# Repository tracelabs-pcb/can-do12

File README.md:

# CAN-DO12 — 24V Aktor-Modul (12x High-Side Digital Outputs)

**Status: PCB-Design abgeschlossen — unbestückt**  
**Tool:** KiCad | **Layer:** 4-Layer | **Hersteller-ready:** Ja

---

## Projektbeschreibung

Kompaktes 24V-Aktormodul zur Ansteuerung von 12 digitalen Lasten 
im Labor- und Prüfstandsbetrieb. Ansteuerung über CAN 2.0B, 
zusätzlich USB-C Service-Port für Parametrierung und Diagnose.
Entwickelt als Prototyp für Prüfstands- und Sondermaschinenbau.

**Besonderheiten:**
- 12x High-Side Ausgänge (24V / 1A je Kanal)
- CAN 2.0B (1 Mbit/s) + USB-C Full-Speed Device
- TVS + Verpolschutz am 24V Eingang
- ESD-Schutz an CAN und USB
- 4-Layer Layout, 140×80mm, Hutschienen-tauglich

---

## Hardware

| Komponente | Beschreibung |
|---|---|
| MCU | USB FS + CAN (STM32-Familie) |
| Ausgangstreiber | 12x High-Side, 24V |
| Schnittstellen | CAN 2.0B, USB-C, SWD |
| Versorgung | 18…30V DC, Buck → 3.3V |
| Schutz | TVS, Verpolschutz, ESD |
| Stackup | 4-Layer (Signal / GND / PWR / Signal) |
| Tool | KiCad |

---

## Anschlüsse

- USB-C (kurze Kante, mittig)
- DE-9 CAN-Stecker
- 2-pol Schraubklemme 24V Eingang
- 2x 8-pol Schraubklemme Ausgänge
- SWD Header (2.54mm)
- Jumper CAN-Terminierung 120Ω

---

## Ausschlüsse

Kein Serienprodukt — kein CE/EMV, keine Safety-Anwendung,
keine galvanische Trennung, keine Firmware.

---

## Dateien in diesem Repository

- `/kicad/` — KiCad Projektdateien
- `/screenshots/` — PCB- und Schematic-Ansichten

---

> Entwickelt von [Shawn Schneider](https://tracelabs-pcb.de)  
> — PCB-Design & Lötservice, Wolfsburg

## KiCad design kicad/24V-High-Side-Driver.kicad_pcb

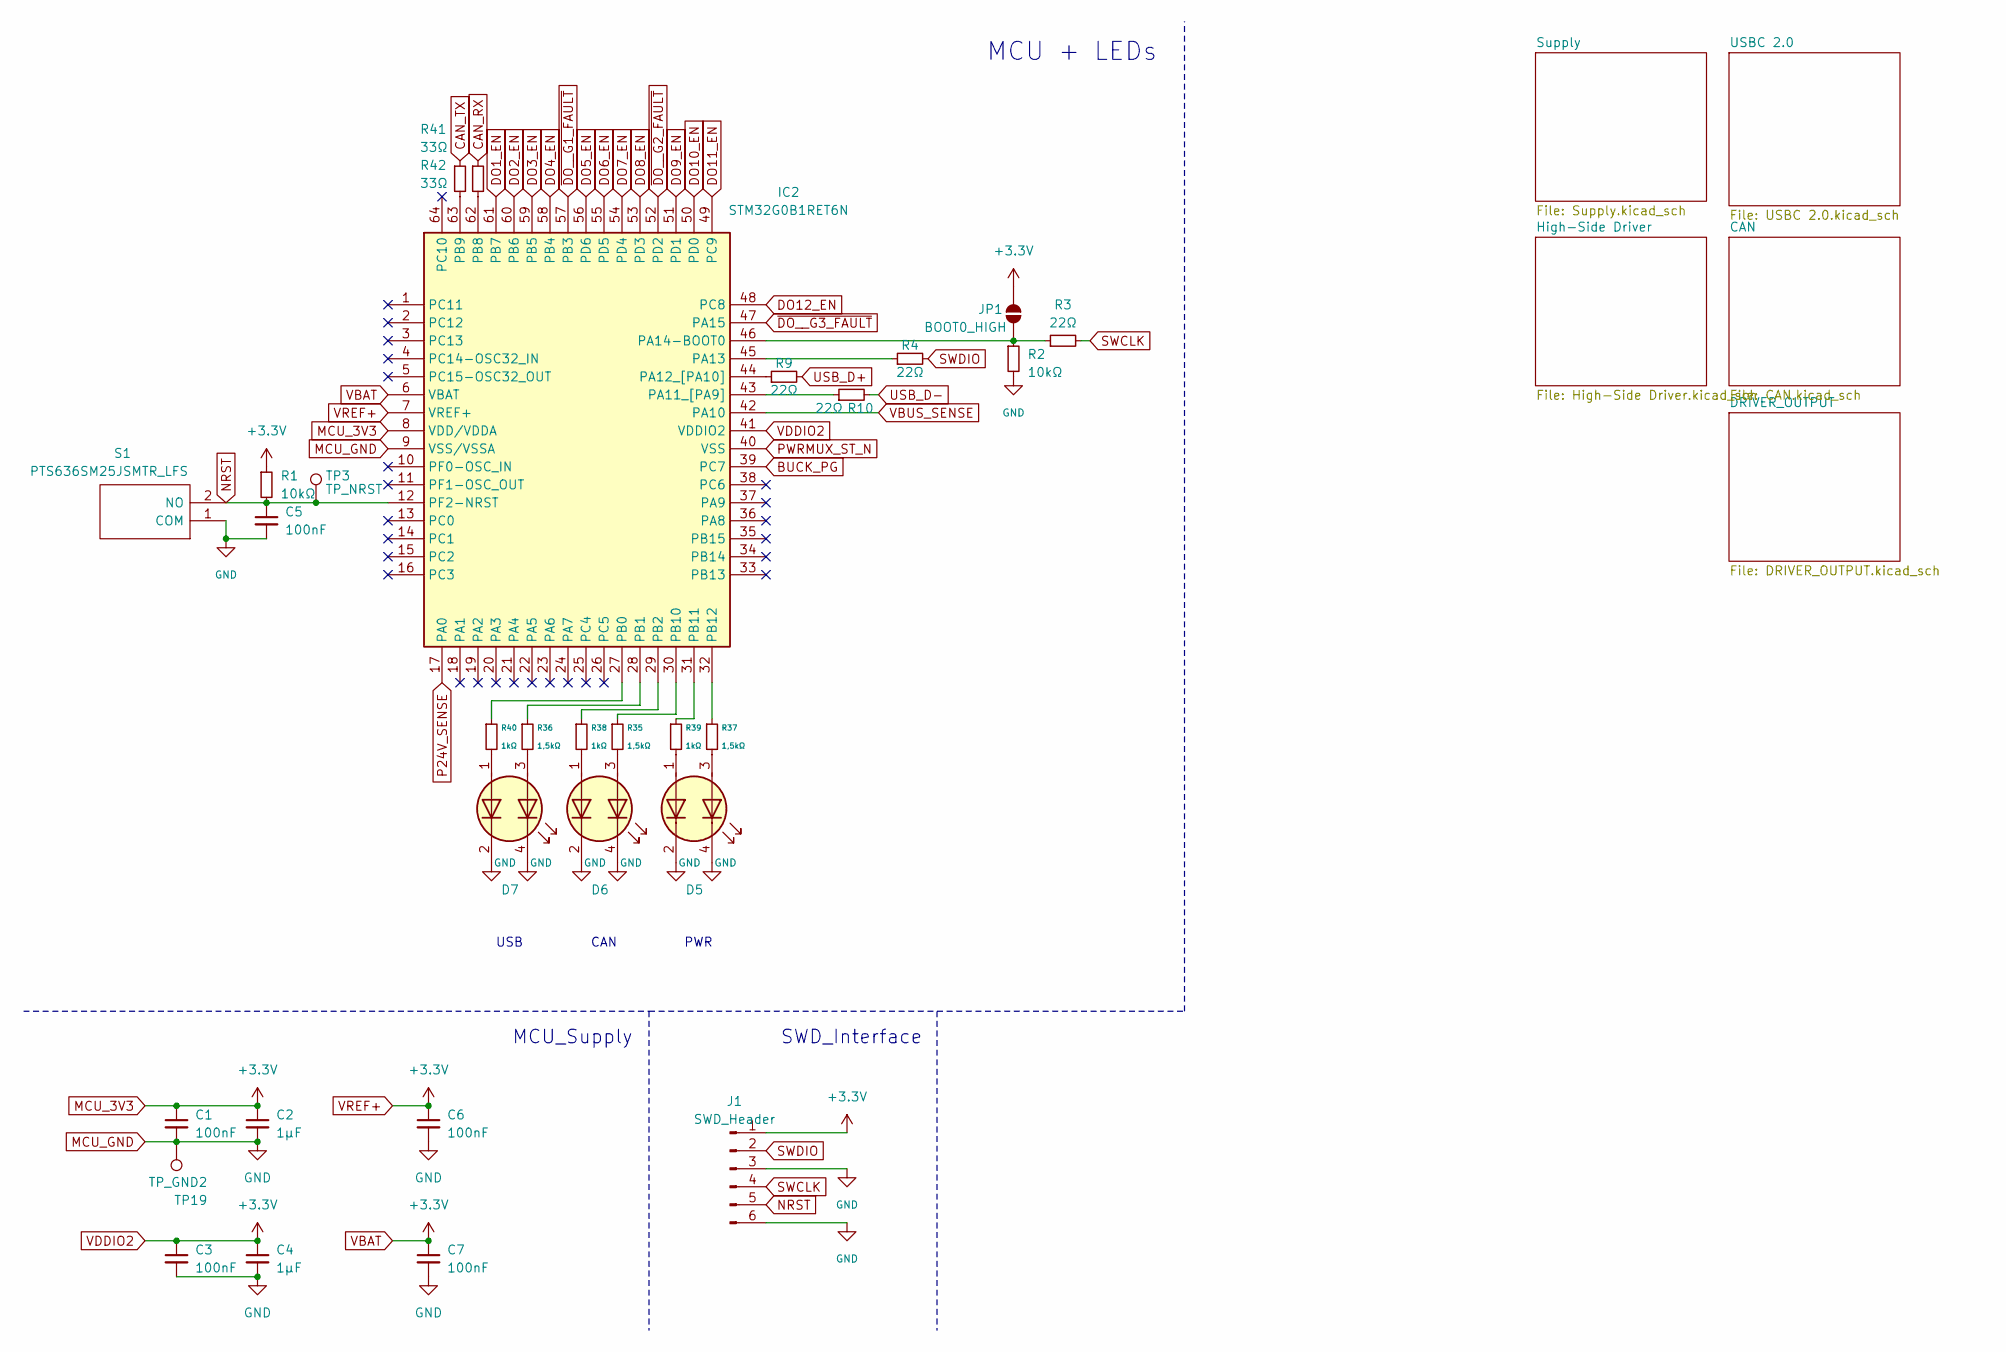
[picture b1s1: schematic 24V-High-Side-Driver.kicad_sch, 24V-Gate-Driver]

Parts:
C1, C3, C5, C6, C7: 100nF; C_0603_1608Metric
C2, C4: 1µF; C_0603_1608Metric
D5, D6, D7: APTBD3216SURKCGKC-01; APTBD3216SURKCGKC01
IC2: STM32G0B1RET6N; QFP50P1200X1200X160-64N; Mouser Part Number 511-STM32G0B1RET6N
J1: SWD_Header; PinHeader_1x06_P2.54mm_Vertical
JP1: BOOT0_HIGH; SolderJumper-2_P1.3mm_Open_RoundedPad1.0x1.5mm
R1, R2: 10kΩ; R_0603_1608Metric
R3, R4, R9, R10: 22Ω; R_0603_1608Metric
R35, R36, R37: 1,5kΩ; R_0603_1608Metric
R38, R39, R40: 1kΩ; R_0603_1608Metric
R41, R42: 33Ω; R_0603_1608Metric
S1: PTS636SM25JSMTR_LFS; PTS636SM25JSMTRLFS; Manufacturer_Part_Number PTS636SM25JSMTR LFS
TP3: TP_NRST; TestPoint_Pad_D1.5mm
TP19: TP_GND2; TestPoint_Pad_D1.5mm

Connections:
BUCK_PG: IC2.39 (PC7); also elsewhere on the board
CAN_RX: R41.1; also elsewhere on the board
CAN_TX: R42.1; also elsewhere on the board
DO1_EN: IC2.61 (PB7); also elsewhere on the board
DO2_EN: IC2.60 (PB6); also elsewhere on the board
DO3_EN: IC2.59 (PB5); also elsewhere on the board
DO4_EN: IC2.58 (PB4); also elsewhere on the board
DO5_EN: IC2.56 (PD6); also elsewhere on the board
DO6_EN: IC2.55 (PD5); also elsewhere on the board
DO7_EN: IC2.54 (PD4); also elsewhere on the board
DO8_EN: IC2.53 (PD3); also elsewhere on the board
DO9_EN: IC2.51 (PD1); also elsewhere on the board
DO10_EN: IC2.50 (PD0); also elsewhere on the board
DO11_EN: IC2.49 (PC9); also elsewhere on the board
DO12_EN: IC2.48 (PC8); also elsewhere on the board
MCU_3V3: C1.1, C2.1, C3.1, C4.1, C6.1, C7.1, IC2.6 (VBAT), IC2.7 (VREF+), IC2.8 (VDD/VDDA), IC2.41 (VDDIO2), J1.1, JP1.2 (B), R1.1; also elsewhere on the board
MCU_GND: C1.2, C2.2, C3.2, C4.2, C5.2, C6.2, C7.2, D5.2 (K1), D5.4 (K2), D6.2 (K1), D6.4 (K2), D7.2 (K1), D7.4 (K2), IC2.9 (VSS/VSSA), J1.3, J1.6, R2.2, S1.1 (COM), TP19.1; also elsewhere on the board
NRST: C5.1, IC2.12 (PF2-NRST), J1.5, R1.2, S1.2 (NO), TP3.1
unnamed: D5.1 (A1), R39.2
unnamed: D5.3 (A2), R37.2
unnamed: D6.1 (A1), R38.2
unnamed: D6.3 (A2), R35.2
unnamed: D7.1 (A1), R40.2
unnamed: D7.3 (A2), R36.2
unnamed: IC2.43 (PA11_[PA9]), R10.1
unnamed: IC2.44 (PA12_[PA10]), R9.1
unnamed: IC2.45 (PA13), R4.1
unnamed: IC2.46 (PA14-BOOT0), JP1.1 (A), R2.1, R3.1
unnamed: IC2.27 (PB0), R40.1
unnamed: IC2.28 (PB1), R36.1
unnamed: IC2.29 (PB2), R38.1
unnamed: IC2.62 (PB8), R41.2
unnamed: IC2.63 (PB9), R42.2
unnamed: IC2.30 (PB10), R35.1
unnamed: IC2.31 (PB11), R39.1
unnamed: IC2.32 (PB12), R37.1
P24V_SENSE: IC2.17 (PA0); also elsewhere on the board
PWRMUX_ST_N: IC2.40 (VSS); also elsewhere on the board
SWCLK: J1.4, R3.2
SWDIO: J1.2, R4.2
USB_D+: R9.2; also elsewhere on the board
USB_D-: R10.2; also elsewhere on the board
VBUS_SENSE: IC2.42 (PA10); also elsewhere on the board
~DO__G1_FAULT: IC2.57 (PB3); also elsewhere on the board
~DO__G2_FAULT: IC2.52 (PD2); also elsewhere on the board
~DO__G3_FAULT: IC2.47 (PA15); also elsewhere on the board

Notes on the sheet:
SWD_Interface
MCU_Supply
PWR
CAN
USB
MCU + LEDs

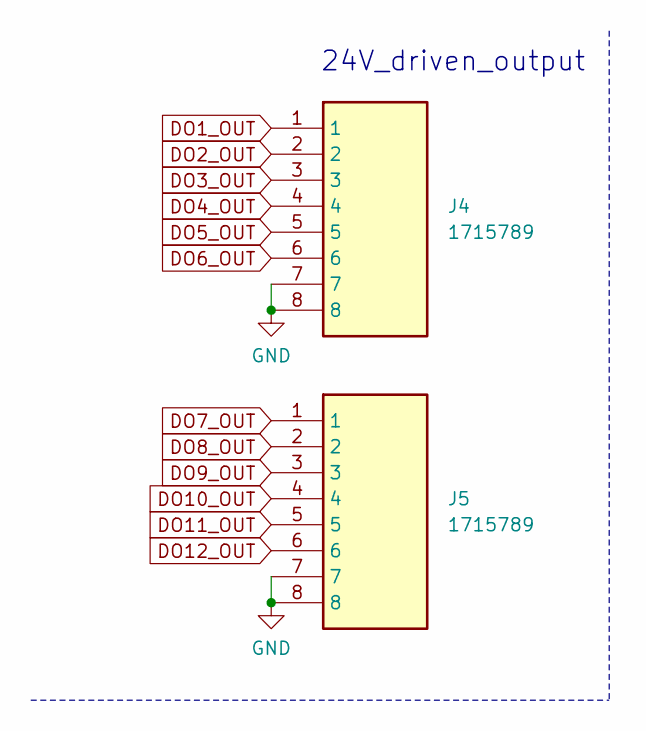
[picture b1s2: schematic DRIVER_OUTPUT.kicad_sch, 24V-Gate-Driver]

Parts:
J4, J5: 1715789; Mouser Part Number 651-1715789

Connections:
DO1_OUT: J4.1; also elsewhere on the board
DO2_OUT: J4.2; also elsewhere on the board
DO3_OUT: J4.3; also elsewhere on the board
DO4_OUT: J4.4; also elsewhere on the board
DO5_OUT: J4.5; also elsewhere on the board
DO6_OUT: J4.6; also elsewhere on the board
DO7_OUT: J5.1; also elsewhere on the board
DO8_OUT: J5.2; also elsewhere on the board
DO9_OUT: J5.3; also elsewhere on the board
DO10_OUT: J5.4; also elsewhere on the board
DO11_OUT: J5.5; also elsewhere on the board
DO12_OUT: J5.6; also elsewhere on the board
MCU_GND: J4.7, J4.8, J5.7, J5.8; also elsewhere on the board

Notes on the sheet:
24V_driven_output

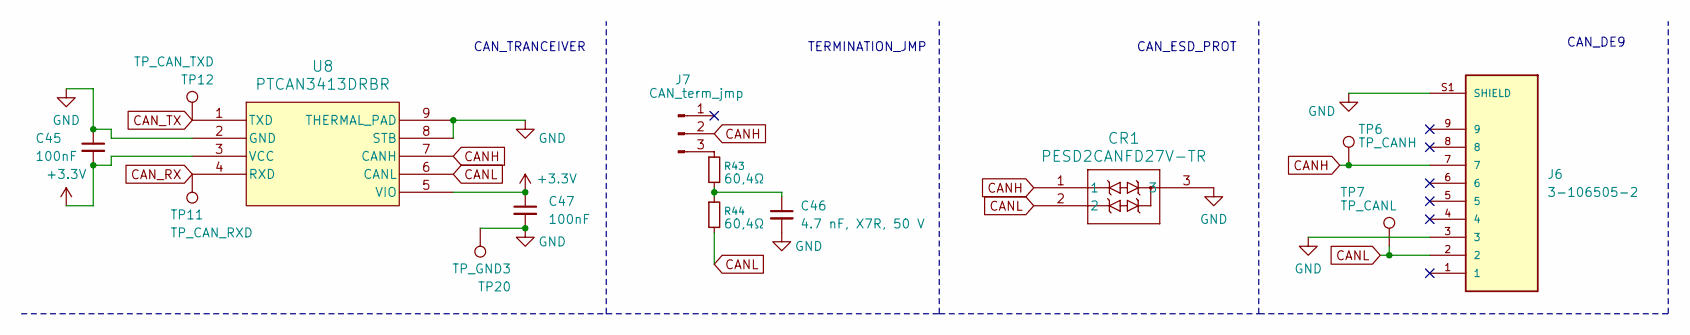
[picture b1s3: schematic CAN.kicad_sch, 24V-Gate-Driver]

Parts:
C45, C47: 100nF; C_0603_1608Metric
C46: 4.7 nF, X7R, 50 V; C_0603_1608Metric
CR1: PESD2CANFD27V-TR; SOT23_PESD2_NEX
J6: 3-106505-2; TE_3-106505-2; PART_REV M; DigiKey_Part_Number A105026-ND
J7: CAN_term_jmp; PinHeader_1x03_P2.54mm_Vertical
R43, R44: 60,4Ω; R_0603_1608Metric
TP6: TP_CANH; TestPoint_Pad_D1.5mm
TP7: TP_CANL; TestPoint_Pad_D1.5mm
TP11: TP_CAN_RXD; TestPoint_Pad_D1.5mm
TP12: TP_CAN_TXD; TestPoint_Pad_D1.5mm
TP20: TP_GND3; TestPoint_Pad_D1.5mm
U8: PTCAN3413DRBR; VSON8-DRB_TEX

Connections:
CANH: CR1.1, J6.7, J7.2, TP6.1, U8.7 (CANH)
CANL: CR1.2, J6.2, R44.2, TP7.1, U8.6 (CANL)
CAN_RX: TP11.1, U8.4 (RXD); also elsewhere on the board
CAN_TX: TP12.1, U8.1 (TXD); also elsewhere on the board
MCU_3V3: C45.2, C47.1, U8.3 (VCC), U8.5 (VIO); also elsewhere on the board
MCU_GND: C45.1, C46.2, C47.2, CR1.3, J6.3, J6.S1 (SHIELD), J6.S2 (SHIELD), TP20.1, U8.2 (GND), U8.8 (STB), U8.9 (THERMAL_PAD); also elsewhere on the board
unnamed: C46.1, R43.2, R44.1
unnamed: J7.3, R43.1

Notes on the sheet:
TERMINATION_JMP
CAN_ESD_PROT
CAN_DE9
CAN_TRANCEIVER

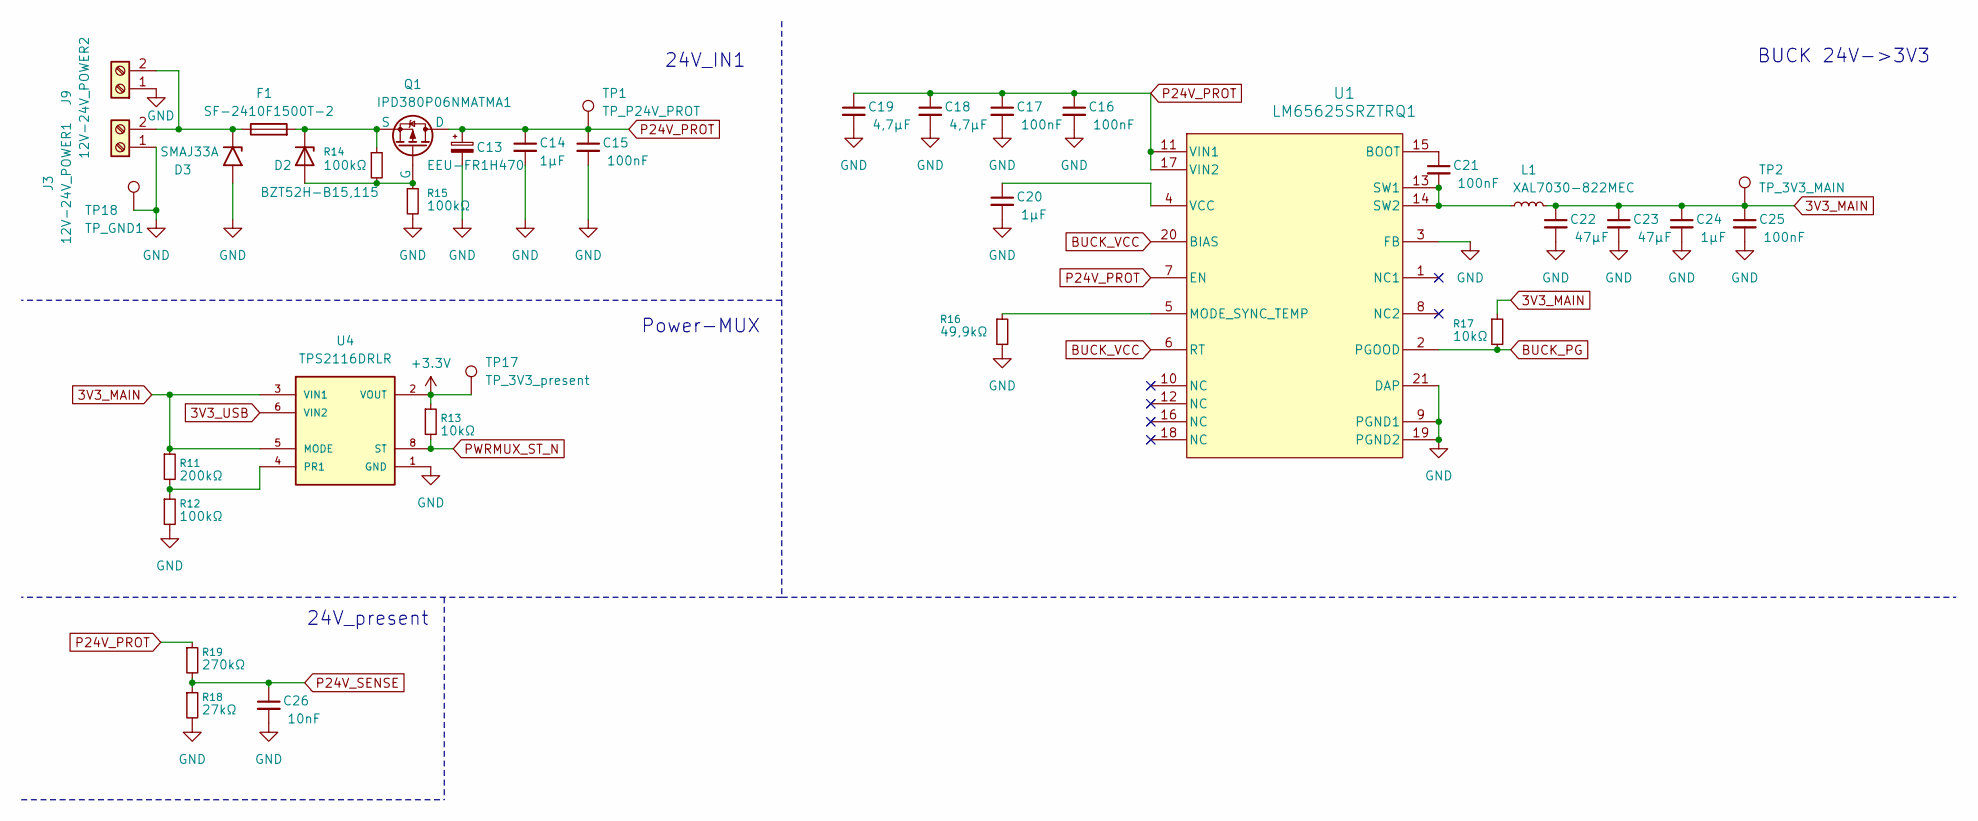
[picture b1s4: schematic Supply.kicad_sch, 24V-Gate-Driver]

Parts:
C13: EEU-FR1H470; CAPPRD250W55D630H1270
C14: 1µF; C_0805_2012Metric
C15, C16, C17, C21, C25: 100nF; C_0603_1608Metric
C18, C19: 4,7µF; C_0805_2012Metric
C20, C24: 1µF; C_0603_1608Metric
C22, C23: 47µF; C_1206_3216Metric
C26: 10nF; C_0603_1608Metric
D2: BZT52H-B15,115; D_SOD-123F
D3: SMAJ33A; D_SMA
F1: SF-2410F1500T-2; SF2410F1500T2
J3: 12V-24V_POWER1; 1729128
J9: 12V-24V_POWER2; 1729128
L1: XAL7030-822MEC; XAL7030822MEC
Q1: IPD380P06NMATMA1; PG-TO252-3-313_INF
R11: 200kΩ; R_0603_1608Metric
R12, R14, R15: 100kΩ; R_0603_1608Metric
R13, R17: 10kΩ; R_0603_1608Metric
R16: 49,9kΩ; R_0603_1608Metric
R18: 27kΩ; R_0603_1608Metric
R19: 270kΩ; R_0603_1608Metric
TP1: TP_P24V_PROT; TestPoint_Pad_D1.5mm
TP2: TP_3V3_MAIN; TestPoint_Pad_D1.5mm
TP17: TP_3V3_present; TestPoint_Pad_D1.5mm
TP18: TP_GND1; TestPoint_Pad_D1.5mm
U1: LM65625SRZTRQ1; RZT0020A-MFG
U4: TPS2116DRLR; SOTFL50P160X60-8N; PARTREV A; DigiKey_Part_Number 296-TPS2116DRLRCT-ND

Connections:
3V3_MAIN: C22.1, C23.1, C24.1, C25.1, L1.2, R11.1, R17.1, TP2.1, U4.3 (VIN1), U4.5 (MODE)
3V3_USB: U4.6 (VIN2); also elsewhere on the board
BUCK_PG: R17.2, U1.2 (PGOOD); also elsewhere on the board
BUCK_VCC: U1.6 (RT), U1.20 (BIAS)
MCU_3V3: R13.1, TP17.1, U4.2 (VOUT), U4.7 (VOUT); also elsewhere on the board
MCU_GND: C13.2, C14.2, C15.2, C16.2, C17.2, C18.2, C19.2, C20.2, C22.2, C23.2, C24.2, C25.2, C26.2, D3.2 (A2), J3.1, J9.1, R12.2, R15.2, R16.2, R18.2, TP18.1, U1.3 (FB), U1.9 (PGND1), U1.19 (PGND2), U1.21 (DAP), U1.22 (DAP), U1.23 (DAP), U1.24 (DAP), U1.25 (DAP), U1.26 (DAP), U1.27 (DAP), U4.1 (GND); also elsewhere on the board
unnamed: D2.2 (A), Q1.1 (G), R14.2, R15.1
unnamed: D2.1 (K), F1.2, Q1.3 (S), R14.1
unnamed: D3.1 (A1), F1.1, J3.2, J9.2
unnamed: C21.1, U1.15 (BOOT)
unnamed: R16.1, U1.5 (MODE_SYNC_TEMP)
unnamed: C21.2, L1.1, U1.13 (SW1), U1.14 (SW2)
unnamed: C20.1, U1.4 (VCC)
unnamed: R11.2, R12.1, U4.4 (PR1)
P24V_PROT: C13.1, C14.1, C15.1, C16.1, C17.1, C18.1, C19.1, Q1.2 (D), R19.1, TP1.1, U1.7 (EN), U1.11 (VIN1), U1.17 (VIN2); also elsewhere on the board
P24V_SENSE: C26.1, R18.1, R19.2; also elsewhere on the board
PWRMUX_ST_N: R13.2, U4.8 (ST); also elsewhere on the board

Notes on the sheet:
BUCK 24V->3V3
24V_IN1
Power-MUX
24V_present

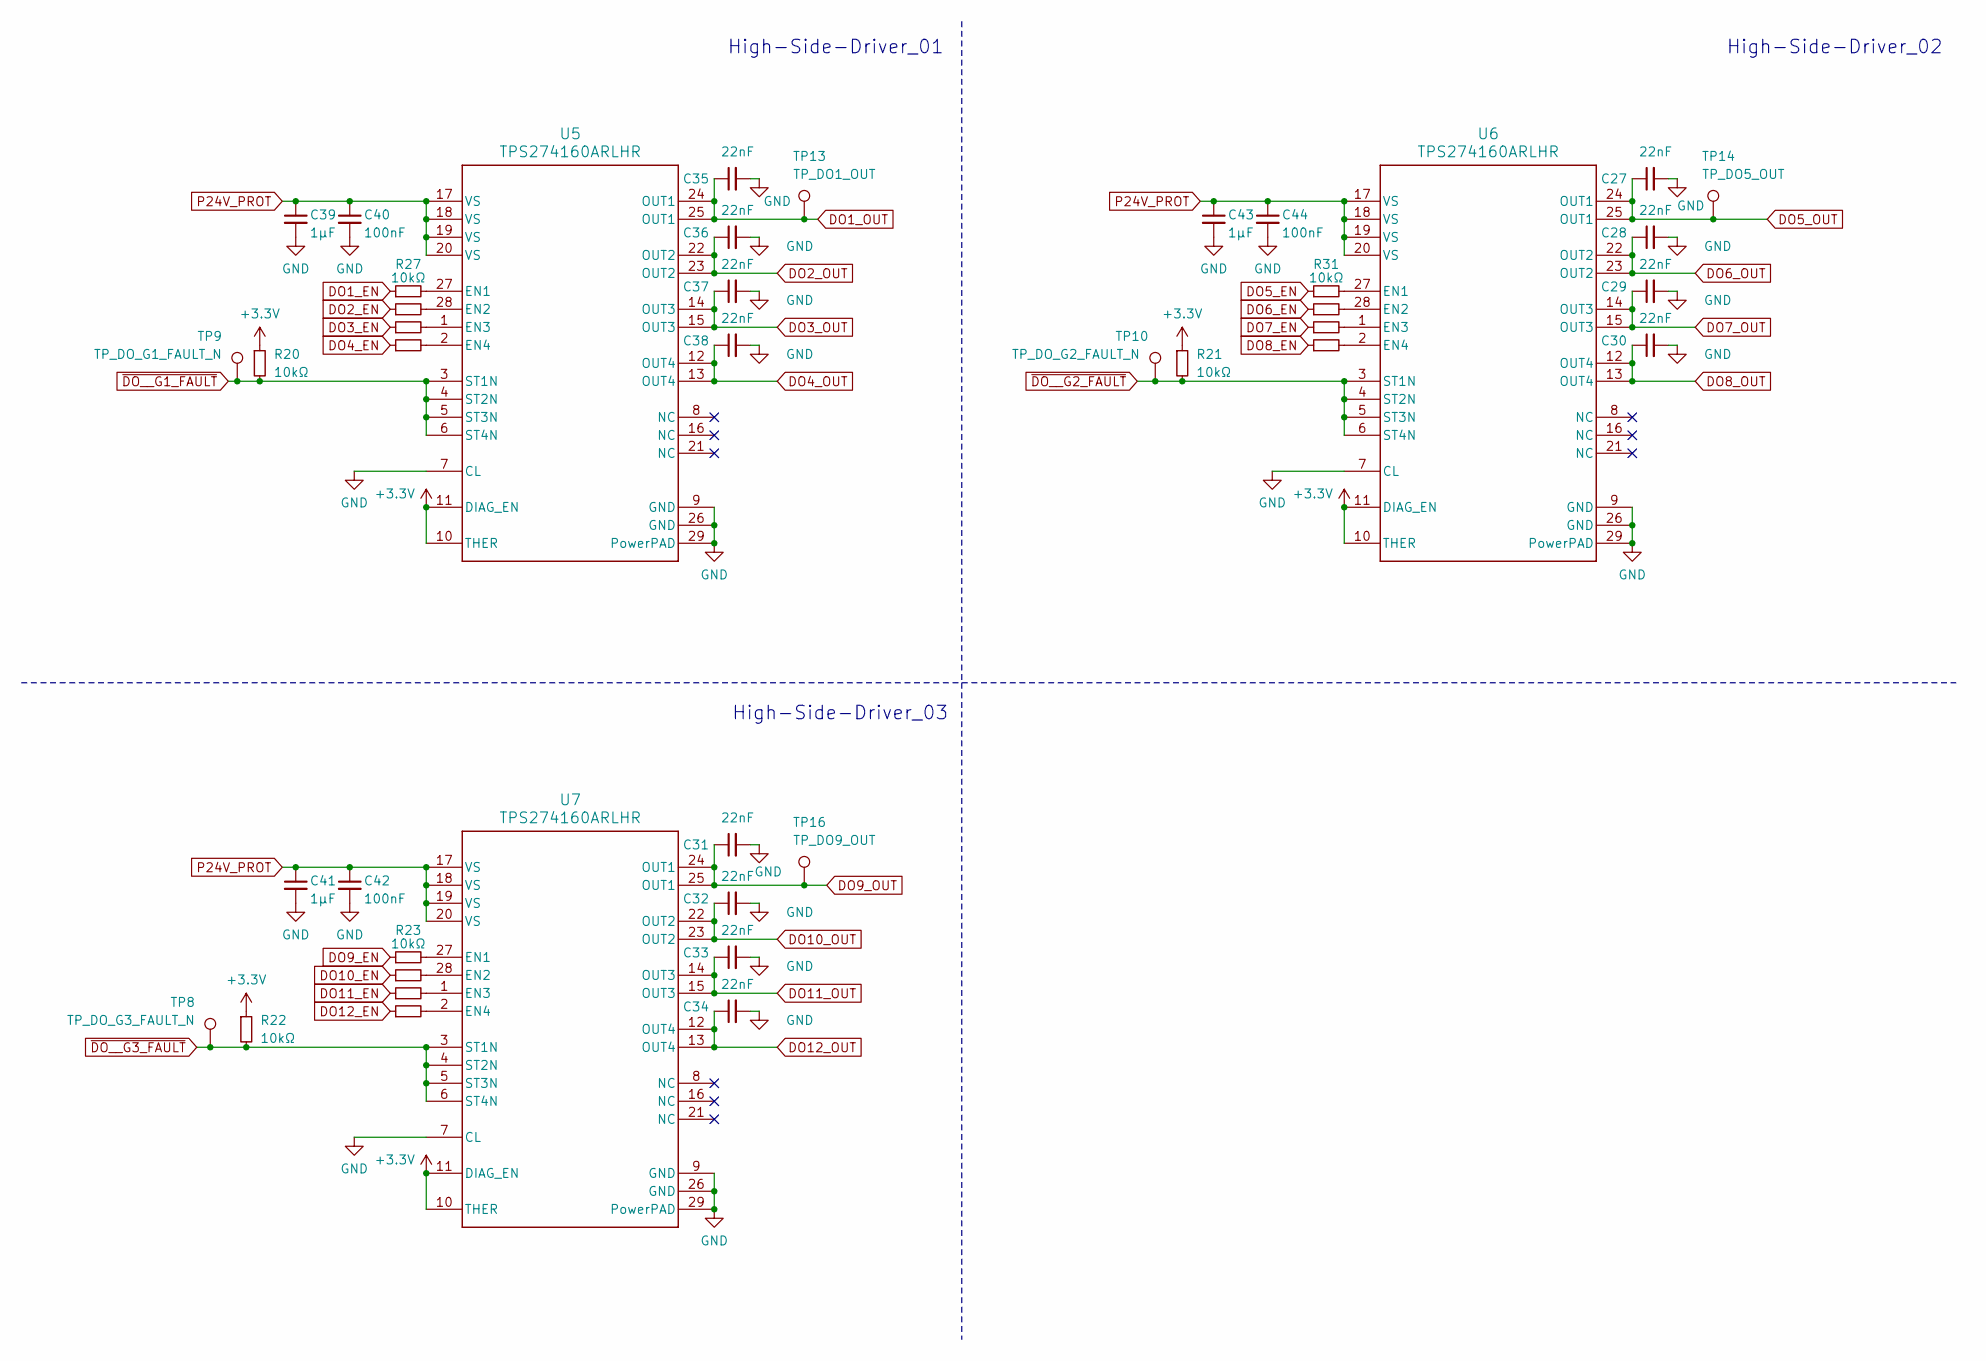
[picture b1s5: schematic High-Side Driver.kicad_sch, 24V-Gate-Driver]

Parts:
C27, C28, C29, C30, C31, C32, C33, C34, C35, C36, C37, C38: 22nF; C_0603_1608Metric
C39, C41, C43: 1µF; C_0805_2012Metric
C40, C42, C44: 100nF; C_0603_1608Metric
R20, R21, R22, R23, R24, R25, R26, R27, R28, R29, R30, R31, R32, R33, R34: 10kΩ; R_0603_1608Metric
TP8: TP_DO_G3_FAULT_N; TestPoint_Pad_D1.5mm
TP9: TP_DO_G1_FAULT_N; TestPoint_Pad_D1.5mm
TP10: TP_DO_G2_FAULT_N; TestPoint_Pad_D1.5mm
TP13: TP_DO1_OUT; TestPoint_Pad_D1.5mm
TP14: TP_DO5_OUT; TestPoint_Pad_D1.5mm
TP16: TP_DO9_OUT; TestPoint_Pad_D1.5mm
U5, U6, U7: TPS274160ARLHR; RLH0028A-MFG

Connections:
DO1_EN: R27.1; also elsewhere on the board
DO1_OUT: C35.1, TP13.1, U5.24 (OUT1), U5.25 (OUT1); also elsewhere on the board
DO2_EN: R28.1; also elsewhere on the board
DO2_OUT: C36.1, U5.22 (OUT2), U5.23 (OUT2); also elsewhere on the board
DO3_EN: R29.1; also elsewhere on the board
DO3_OUT: C37.1, U5.14 (OUT3), U5.15 (OUT3); also elsewhere on the board
DO4_EN: R30.1; also elsewhere on the board
DO4_OUT: C38.1, U5.12 (OUT4), U5.13 (OUT4); also elsewhere on the board
DO5_EN: R31.1; also elsewhere on the board
DO5_OUT: C27.1, TP14.1, U6.24 (OUT1), U6.25 (OUT1); also elsewhere on the board
DO6_EN: R32.1; also elsewhere on the board
DO6_OUT: C28.1, U6.22 (OUT2), U6.23 (OUT2); also elsewhere on the board
DO7_EN: R33.1; also elsewhere on the board
DO7_OUT: C29.1, U6.14 (OUT3), U6.15 (OUT3); also elsewhere on the board
DO8_EN: R34.1; also elsewhere on the board
DO8_OUT: C30.1, U6.12 (OUT4), U6.13 (OUT4); also elsewhere on the board
DO9_EN: R23.1; also elsewhere on the board
DO9_OUT: C31.1, TP16.1, U7.24 (OUT1), U7.25 (OUT1); also elsewhere on the board
DO10_EN: R24.1; also elsewhere on the board
DO10_OUT: C32.1, U7.22 (OUT2), U7.23 (OUT2); also elsewhere on the board
DO11_EN: R25.1; also elsewhere on the board
DO11_OUT: C33.1, U7.14 (OUT3), U7.15 (OUT3); also elsewhere on the board
DO12_EN: R26.1; also elsewhere on the board
DO12_OUT: C34.1, U7.12 (OUT4), U7.13 (OUT4); also elsewhere on the board
MCU_3V3: R20.1, R21.1, R22.1, U5.10 (THER), U5.11 (DIAG_EN), U6.10 (THER), U6.11 (DIAG_EN), U7.10 (THER), U7.11 (DIAG_EN); also elsewhere on the board
MCU_GND: C27.2, C28.2, C29.2, C30.2, C31.2, C32.2, C33.2, C34.2, C35.2, C36.2, C37.2, C38.2, C39.2, C40.2, C41.2, C42.2, C43.2, C44.2, U5.7 (CL), U5.9 (GND), U5.26 (GND), U5.29 (PowerPAD), U5.30 (GND), U5.31 (GND), U5.32 (GND), U5.33 (GND), U5.34 (GND), U5.35 (GND), U5.36 (GND), U5.37 (GND), U6.7 (CL), U6.9 (GND), U6.26 (GND), U6.29 (PowerPAD), U6.30 (GND), U6.31 (GND), U6.32 (GND), U6.33 (GND), U6.34 (GND), U6.35 (GND), U6.36 (GND), U6.37 (GND), U7.7 (CL), U7.9 (GND), U7.26 (GND), U7.29 (PowerPAD), U7.30 (GND), U7.31 (GND), U7.32 (GND), U7.33 (GND), U7.34 (GND), U7.35 (GND), U7.36 (GND), U7.37 (GND); also elsewhere on the board
unnamed: R27.2, U5.27 (EN1)
unnamed: R28.2, U5.28 (EN2)
unnamed: R29.2, U5.1 (EN3)
unnamed: R30.2, U5.2 (EN4)
unnamed: R31.2, U6.27 (EN1)
unnamed: R32.2, U6.28 (EN2)
unnamed: R33.2, U6.1 (EN3)
unnamed: R34.2, U6.2 (EN4)
unnamed: R23.2, U7.27 (EN1)
unnamed: R24.2, U7.28 (EN2)
unnamed: R25.2, U7.1 (EN3)
unnamed: R26.2, U7.2 (EN4)
P24V_PROT: C39.1, C40.1, C41.1, C42.1, C43.1, C44.1, U5.17 (VS), U5.18 (VS), U5.19 (VS), U5.20 (VS), U6.17 (VS), U6.18 (VS), U6.19 (VS), U6.20 (VS), U7.17 (VS), U7.18 (VS), U7.19 (VS), U7.20 (VS); also elsewhere on the board
~DO__G1_FAULT: R20.2, TP9.1, U5.3 (ST1N), U5.4 (ST2N), U5.5 (ST3N), U5.6 (ST4N); also elsewhere on the board
~DO__G2_FAULT: R21.2, TP10.1, U6.3 (ST1N), U6.4 (ST2N), U6.5 (ST3N), U6.6 (ST4N); also elsewhere on the board
~DO__G3_FAULT: R22.2, TP8.1, U7.3 (ST1N), U7.4 (ST2N), U7.5 (ST3N), U7.6 (ST4N); also elsewhere on the board

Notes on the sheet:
High-Side-Driver_03
High-Side-Driver_02
High-Side-Driver_01

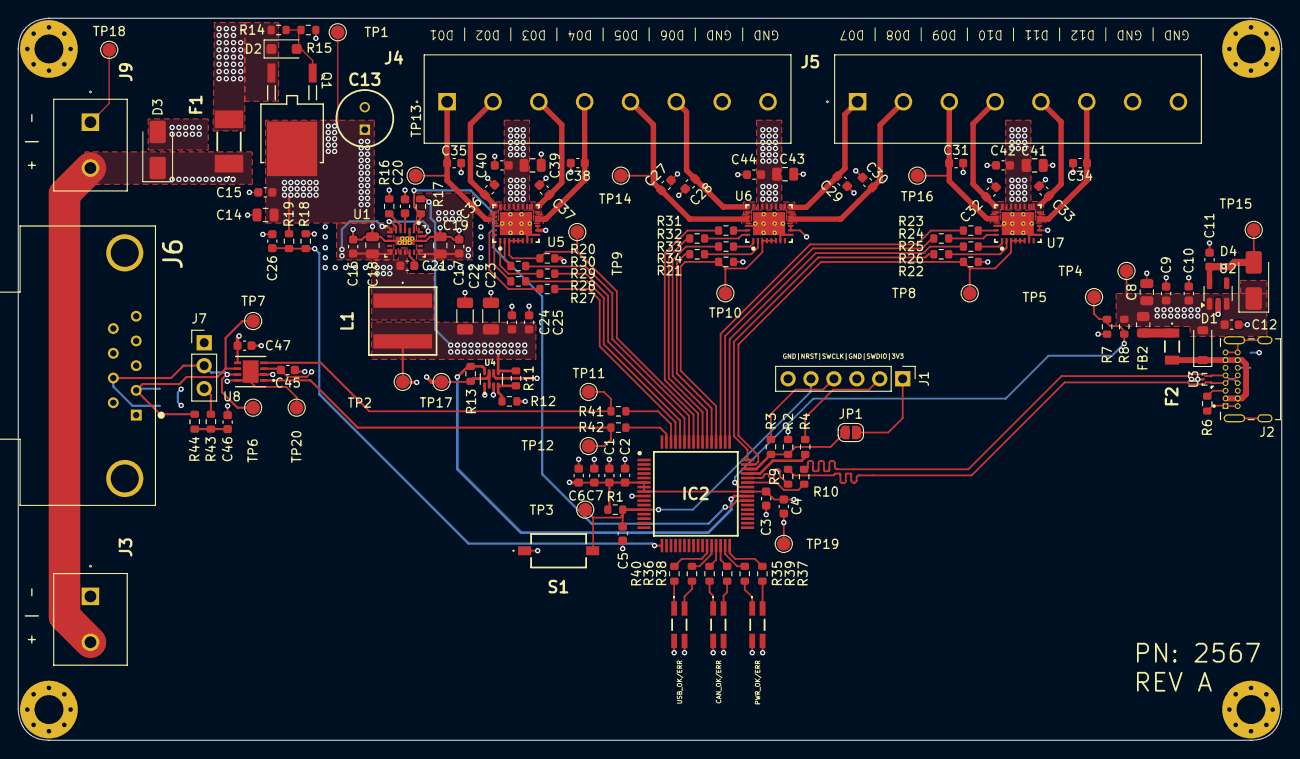
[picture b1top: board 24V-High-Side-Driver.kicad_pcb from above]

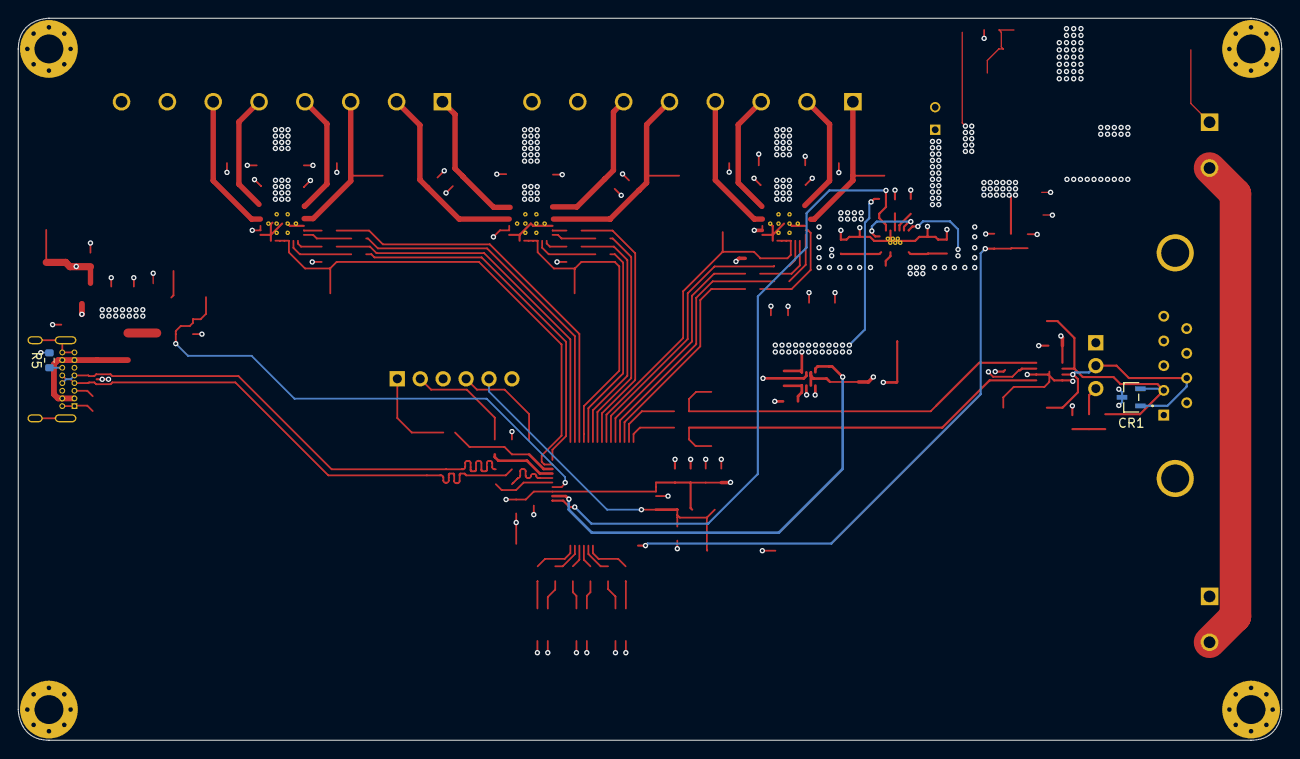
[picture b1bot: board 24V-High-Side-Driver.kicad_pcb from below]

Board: 4 copper layers, 140.0 x 80.0 mm, 143 parts (2 on the bottom side), 91 nets.

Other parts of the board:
C8: 10µF; C_0805_2012Metric
C9, C11, C12: 1µF; C_0603_1608Metric
C10: 100nF; C_0603_1608Metric
D1: Littelfuse SMF5.0A; D_SOD-123
D4: SS14; D_SMA
F2: MF-MSMF050/40X-2; MFNSMF07513X2
FB2: BLM21PG121SN1D; R_0805_2012Metric
J2: UJ20-C-H-G-SMT-TR; CUI_UJ20-C-H-G-SMT-TR
R5, R6: 5,1kΩ; R_0603_1608Metric
R7: 120kΩ; R_0603_1608Metric
R8: 100kΩ; R_0603_1608Metric
TP4: TP_USB_VBUS; TestPoint_Pad_D1.5mm
TP5: TP_VBUS_SENSE; TestPoint_Pad_D1.5mm
TP15: TP_3V3_USB; TestPoint_Pad_D1.5mm
U2: TLV75533PDBV; SOT-23-5
U3: TPD2EUSB30; Texas_DRT-3

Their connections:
3V3_USB: C11.1, D4.2 (A), TP15.1, U2.5 (OUT); also elsewhere on the board
MCU_GND: C8.2, C9.2, C10.2, C11.2, C12.2, J2.A1 (GND), J2.A12 (GND), J2.B1 (GND), J2.B12 (GND), J2.SH1 (SHIELD), J2.SH2 (SHIELD), J2.SH3 (SHIELD), J2.SH4 (SHIELD), R5.2, R6.2, R7.1, U2.2 (GND), U3.3 (GND); also elsewhere on the board
unnamed: F2.1, FB2.1
unnamed: J2.A5 (CC1), R6.1
unnamed: J2.B5 (CC2), R5.1
USB_D+: J2.A6 (DP1), J2.B6 (DP2), U3.1 (D+); also elsewhere on the board
USB_D-: J2.A7 (DN1), J2.B7 (DN2), U3.2 (D-); also elsewhere on the board
VBUS: D1.1 (A1), F2.2, J2.A4 (VBUS), J2.A9 (VBUS), J2.B4 (VBUS), J2.B9 (VBUS)
VBUS_5V: C8.1, C9.1, C10.1, C12.1, D1.2 (A2), D4.1 (K), FB2.2, R8.2, TP4.1, U2.1 (IN), U2.3 (EN)
VBUS_SENSE: R7.2, R8.1, TP5.1; also elsewhere on the board

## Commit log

2026-03-24 Add CAN-DO12 project README
2026-03-24 Add screenshots folder
2026-03-24 Add project screenshots
2026-03-24 Add kicad folder
2026-03-24 Add KiCad project files
